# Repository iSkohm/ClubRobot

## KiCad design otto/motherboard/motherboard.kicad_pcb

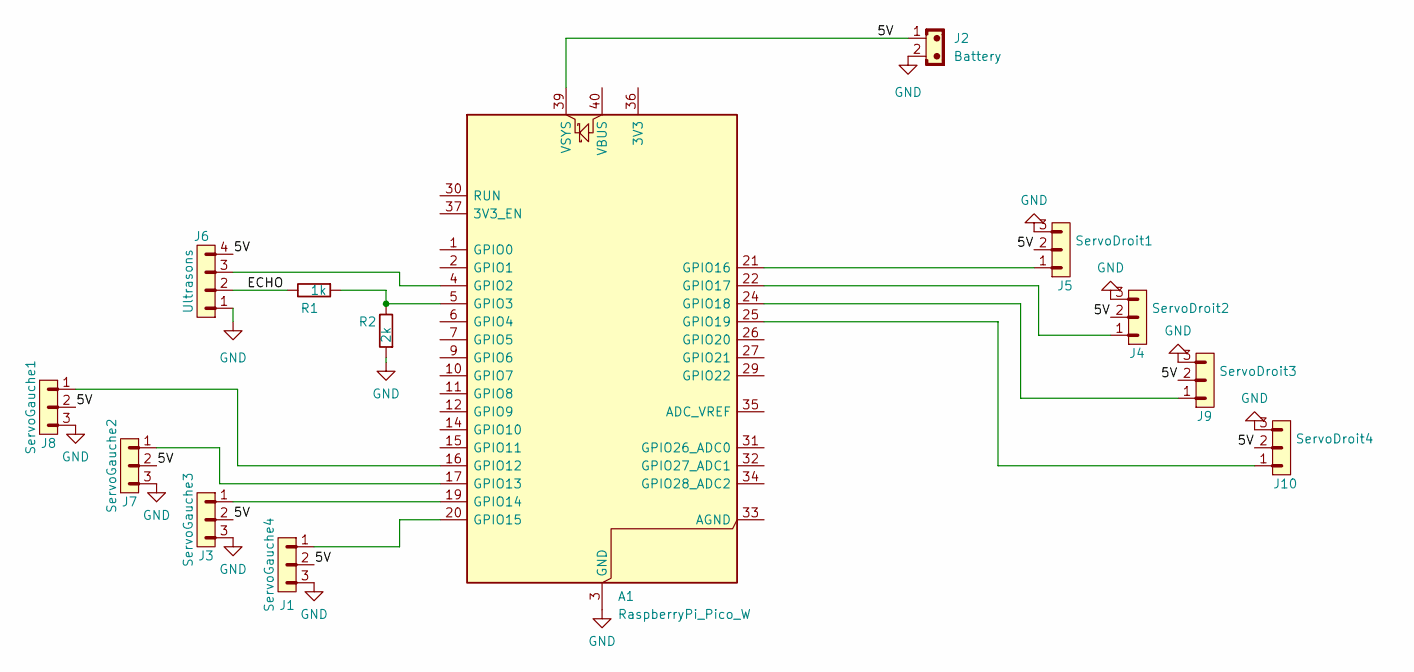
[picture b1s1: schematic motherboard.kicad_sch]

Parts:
A1: RaspberryPi_Pico_W; raspberry_pi_pico_THT
J1: ServoGauche4; PinHeader_1x03_P2.54mm_Vertical
J2: Battery; JST_EH_B2B-EH-A_1x02_P2.50mm_Vertical
J3: ServoGauche3; PinHeader_1x03_P2.54mm_Vertical
J4: ServoDroit2; PinHeader_1x03_P2.54mm_Vertical
J5: ServoDroit1; PinHeader_1x03_P2.54mm_Vertical
J6: Ultrasons; PinHeader_1x04_P2.54mm_Vertical
J7: ServoGauche2; PinHeader_1x03_P2.54mm_Vertical
J8: ServoGauche1; PinHeader_1x03_P2.54mm_Vertical
J9: ServoDroit3; PinHeader_1x03_P2.54mm_Vertical
J10: ServoDroit4; PinHeader_1x03_P2.54mm_Vertical
R1: 1k; R_Axial_DIN0207_L6.3mm_D2.5mm_P10.16mm_Horizontal
R2: 2k; R_Axial_DIN0207_L6.3mm_D2.5mm_P10.16mm_Horizontal

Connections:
/5V: A1.39 (VSYS), J1.2, J2.1, J3.2, J4.2, J5.2, J6.4, J7.2, J8.2, J9.2, J10.2
/ECHO: J6.2, R1.2
GND: A1.3 (GND), A1.8 (GND), A1.13 (GND), A1.18 (GND), A1.23 (GND), A1.28 (GND), A1.38 (GND), J1.3, J2.2, J3.3, J4.3, J5.3, J6.1, J7.3, J8.3, J9.3, J10.3, R2.1
unnamed: A1.4 (GPIO2), J6.3
unnamed: A1.5 (GPIO3), R1.1, R2.2
unnamed: A1.16 (GPIO12), J8.1
unnamed: A1.17 (GPIO13), J7.1
unnamed: A1.19 (GPIO14), J3.1
unnamed: A1.20 (GPIO15), J1.1
unnamed: A1.21 (GPIO16), J5.1
unnamed: A1.22 (GPIO17), J4.1
unnamed: A1.24 (GPIO18), J9.1
unnamed: A1.25 (GPIO19), J10.1

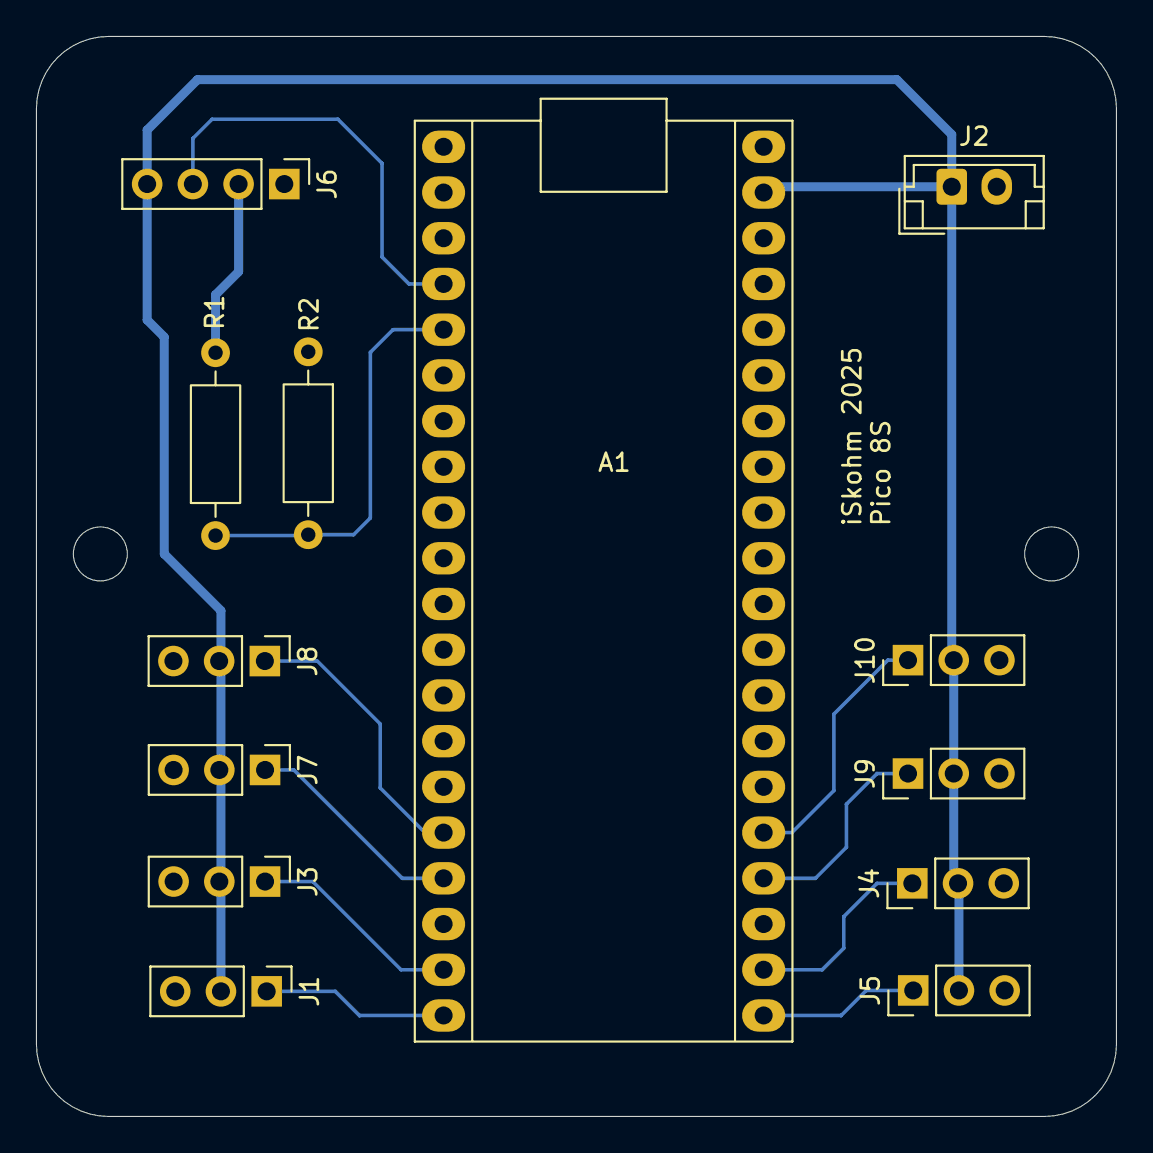
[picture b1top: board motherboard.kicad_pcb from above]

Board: 2 copper layers, 60.0 x 60.0 mm, 13 parts (0 on the bottom side), 13 nets.

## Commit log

2025-09-18 1st lesson
2025-09-18 4th lesson
2025-09-18 lesson 6
2025-09-18 in middle of martocizo
2025-09-19 martocizo ok
2025-09-19 bidi
2025-09-19 martocizo fix
2025-09-19 martocizo works
2025-09-19 martocizo icon fix
2025-10-08 adds classes
2025-10-11 ajoute servo pince
2025-10-11 cleanup
2025-10-11 rm dsstore
2025-10-11 orto
2025-10-12 reorganisation et ajout class servo
2025-10-12 rename et double servo
2025-10-13 ajouter pince telecommandee
2025-10-27 adds otto mb 8servos
2025-10-27 put gbr in folder
2025-11-03 adds otto mb and pico servo code
2026-02-27 Add complete robot.iskohm.com website: lessons, competition, worksheets
2026-02-27 Add GitHub Pages deployment workflow + CNAME for robot.iskohm.com
2026-02-27 Serve site from /docs for GitHub Pages
2026-02-27 Fix code blocks in worksheet: use pre/code + JS highlighter, no raw HTML spans
2026-02-27 Fix syntax highlighter: use placeholders to prevent class/in keywords matching inside span tags
2026-02-27 Replace regex highlighter with proper tokenizer — fixes class=kw visible in code blocks
2026-02-28 feat: adds ClubRobot educational website
2026-02-28 feat: robotic camel logo in hero (big) and nav (small)
2026-02-28 feat: hero camel logo bigger + transparent bg
2026-02-28 fix: remove robot emoji from hero
2026-02-28 fix: Club Robot iSkohm bigger than tagline
2026-02-28 fix: smaller hero tagline
2026-02-28 fix: iSkohm same style as Club Robot in hero
2026-02-28 fix: camel hero logo bigger 380px
2026-02-28 fix: nav camel bigger + trimmed
2026-02-28 fix: nav camel 47px
2026-02-28 fix: camel head centered in hero
2026-02-28 fix: camel logo trimmed and squared for centered hero
2026-02-28 fix: properly trim camel logo to content bounds
2026-02-28 feat: footer logo + Club Robot iSkohm branding
2026-02-28 fix: hero camel 10% smaller
2026-02-28 feat: camel head favicon
2026-02-28 fix: consistent nav logo across all pages
2026-02-28 fix: consistent footer logo across all pages
2026-02-28 fix: footer URL → robot.iskohm.com
2026-02-28 fix: update nav + footer logo on all lesson pages
2026-02-28 feat: 3 teams of 3 on competition page
2026-02-28 fix: replace all Otto mentions with Robot
2026-02-28 fix: 3 robots on competition page
2026-02-28 feat: Raspberry Pi logo before Pico mentions
2026-02-28 feat: micro:bit logo before BBC micro:bit mentions
2026-02-28 feat: host rpi + microbit logos locally
2026-02-28 fix: remove 🫐 and 🔲 emojis
2026-02-28 feat: real logos in component cards
2026-02-28 feat: clickable links on microbit + rpi cards
2026-02-28 fix: working rpi + microbit logos
2026-02-28 fix: proper rpi + microbit logos
2026-02-28 fix: official Raspberry Pi logo from raspberrypi.com
2026-02-28 fix: microbit link → microbit.org/fr/
2026-02-28 fix: official micro:bit stacked logo from Wikipedia
2026-02-28 fix: Raspberry Pi logo with white text
2026-02-28 fix: official Raspberry Pi icon logo
2026-02-28 fix: camel head instead of robot emoji; microbit logo clickable
2026-02-28 fix: rpi logo clickable
2026-02-28 Add Cloudflare Workers configuration
2026-03-09 legal: privacy policy + ToS page, footer link
2026-03-09 legal: remove email address
2026-03-10 cleanup: remove website/ — moved to iSkohm/Robot.git
2026-04-05 PongShoo
2026-04-06 rename, adds 1.5mm wing
